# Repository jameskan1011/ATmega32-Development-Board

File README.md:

# ATmega32-Development-Board
ATmega32 Development Board with Latches and Buffers to minimize GPIO used.

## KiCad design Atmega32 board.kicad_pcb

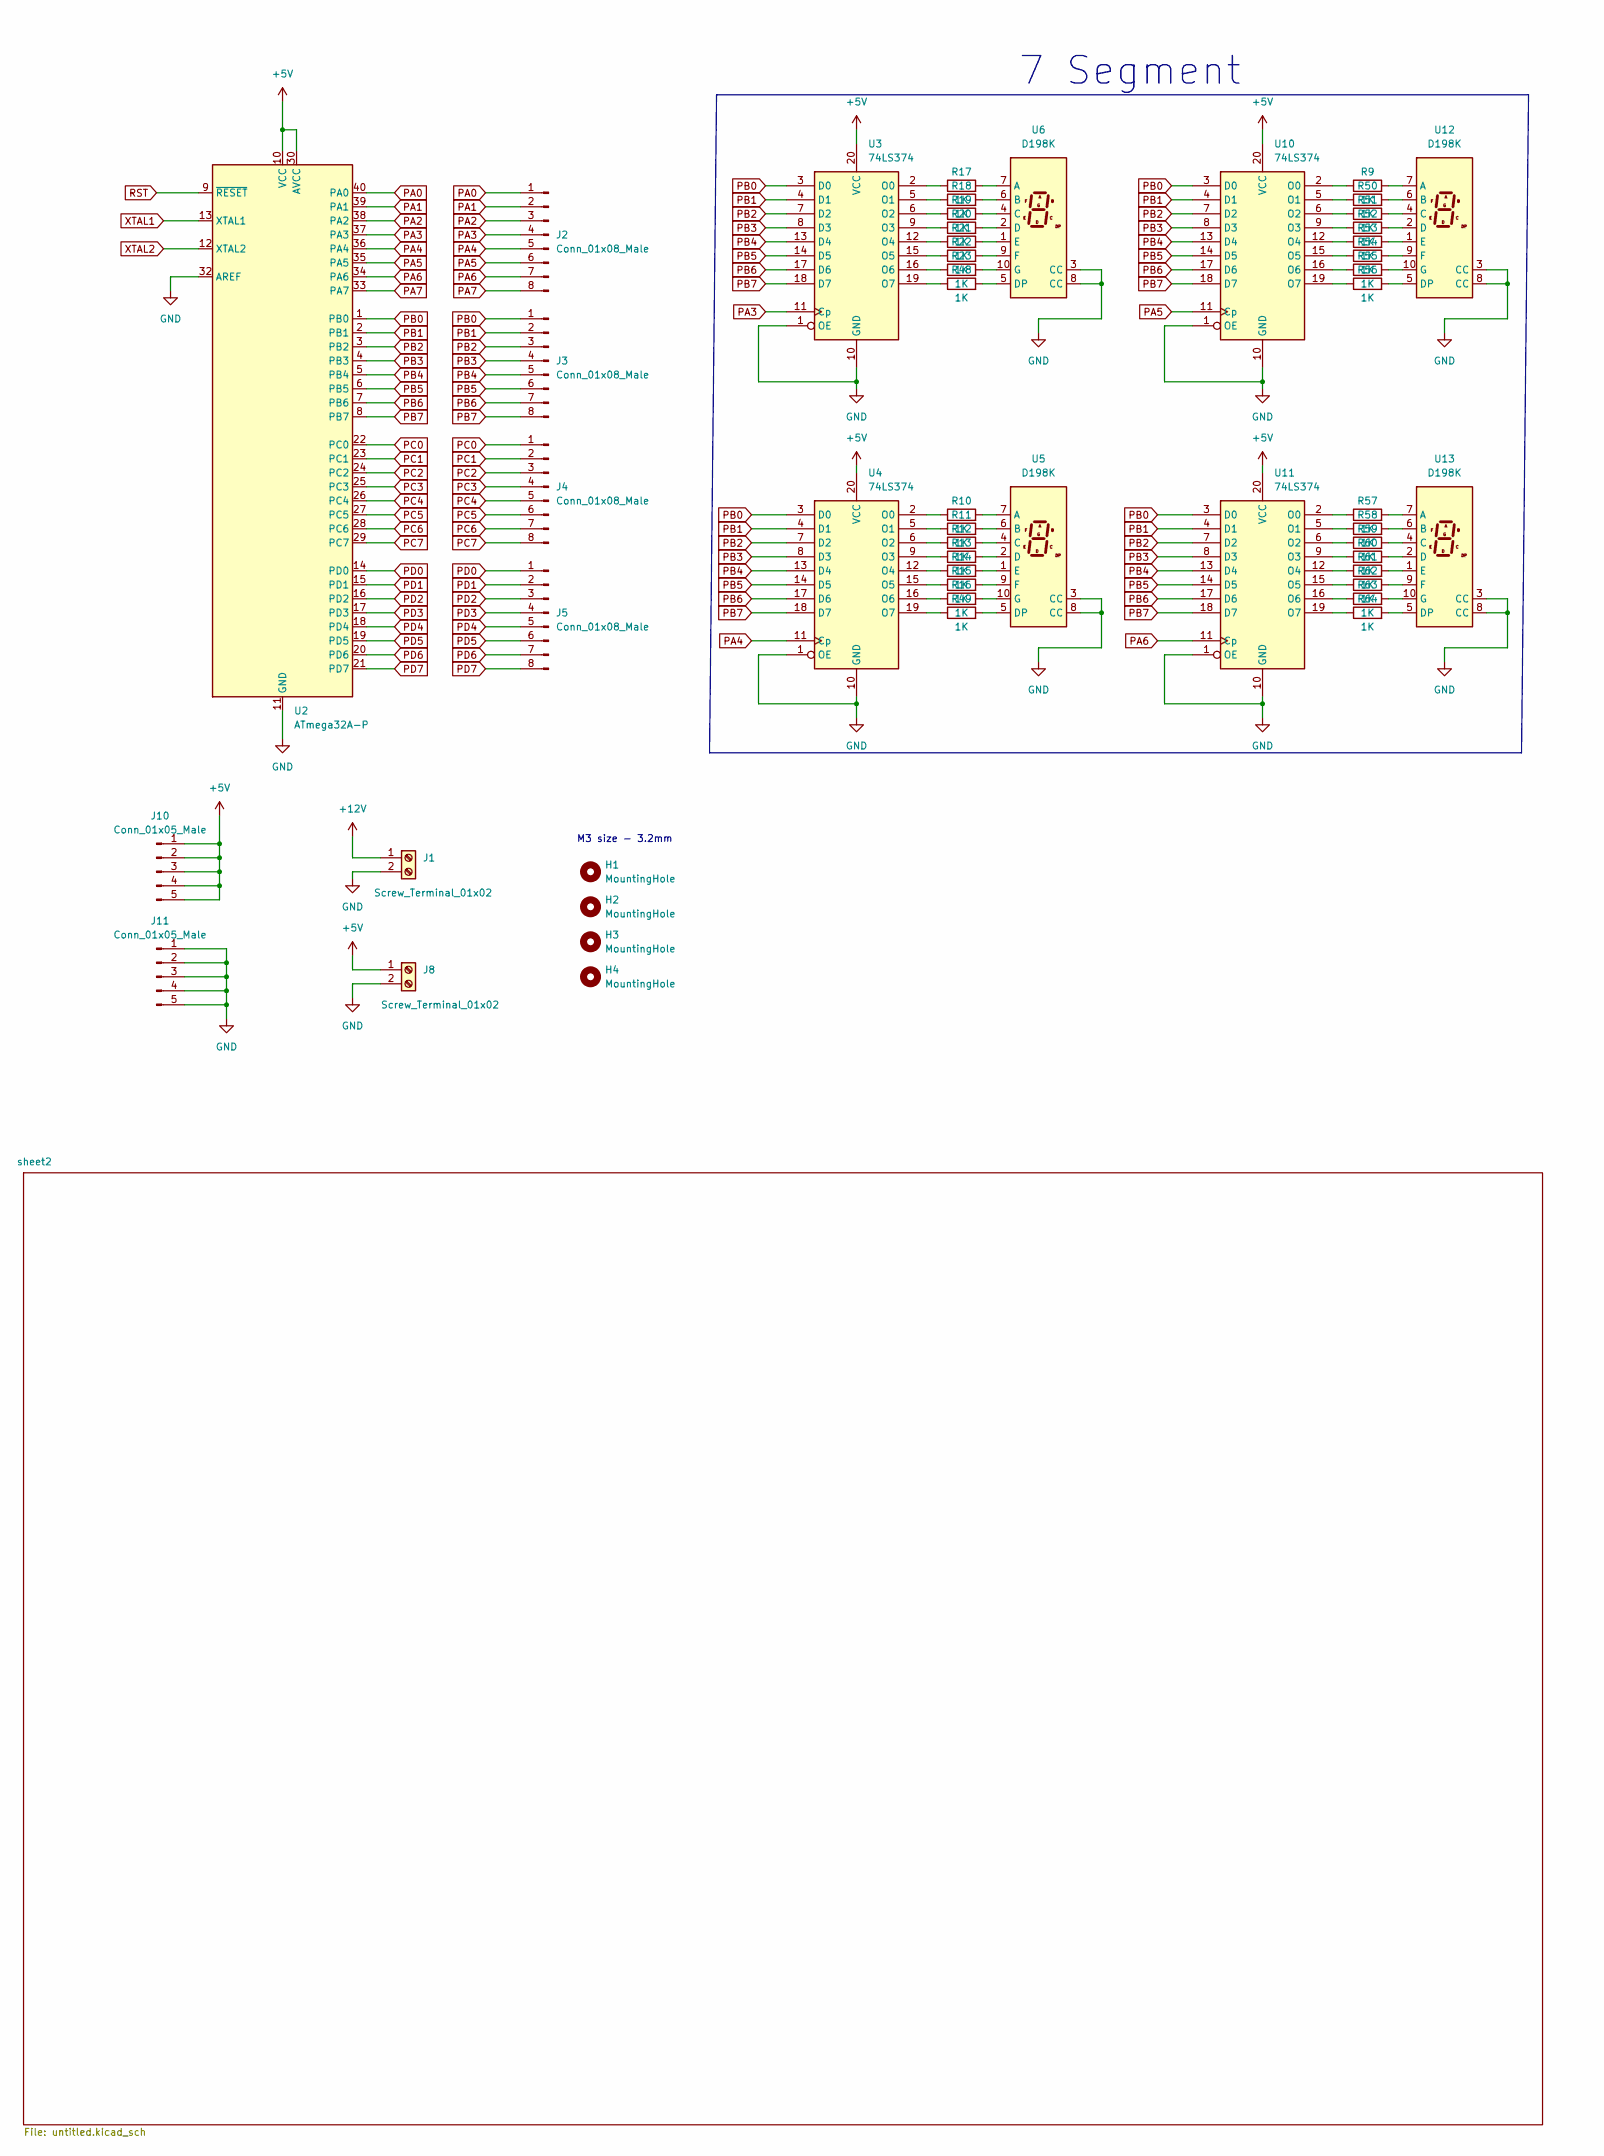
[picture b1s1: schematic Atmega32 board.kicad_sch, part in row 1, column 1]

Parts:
H1, H2, H3, H4: MountingHole; MountingHole_3.2mm_M3
J1, J8: Screw_Terminal_01x02; TerminalBlock_RND_205-00045_1x02_P5.00mm_Horizontal
J2, J3, J4, J5: Conn_01x08_Male; PinHeader_1x08_P2.54mm_Vertical
J10, J11: Conn_01x05_Male; PinHeader_1x05_P2.54mm_Vertical
R9, R10, R11, R12, R13, R14, R15, R16, R17, R18, R19, R20, R21, R22, R23, R48, R49, R50, R51, R52, R53, R54, R55, R56, R57, R58, R59, R60, R61, R62, R63, R64: 1K; R_0805_2012Metric_Pad1.20x1.40mm_HandSolder
U2: ATmega32A-P; DIP-40_W15.24mm
U3, U4, U10, U11: 74LS374; SOIC-20W_7.5x12.8mm_P1.27mm
U5, U6, U12, U13: D198K; 7SegmentLED_LTS6760_LTS6780

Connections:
+5V: J8.1, J10.1, J10.2, J10.3, J10.4, J10.5, U2.10 (VCC), U2.30 (AVCC), U3.20 (VCC), U4.20 (VCC), U10.20 (VCC), U11.20 (VCC); also elsewhere on the board
+12V: J1.1; also elsewhere on the board
GND: J1.2, J8.2, J11.1, J11.2, J11.3, J11.4, J11.5, U2.11 (GND), U2.31 (GND), U2.32 (AREF), U3.1 (OE), U3.10 (GND), U4.1 (OE), U4.10 (GND), U5.3 (CC), U5.8 (CC), U6.3 (CC), U6.8 (CC), U10.1 (OE), U10.10 (GND), U11.1 (OE), U11.10 (GND), U12.3 (CC), U12.8 (CC), U13.3 (CC), U13.8 (CC); also elsewhere on the board
unnamed: R17.1, U3.2 (O0)
unnamed: R18.1, U3.5 (O1)
unnamed: R19.1, U3.6 (O2)
unnamed: R20.1, U3.9 (O3)
unnamed: R21.1, U3.12 (O4)
unnamed: R22.1, U3.15 (O5)
unnamed: R23.1, U3.16 (O6)
unnamed: R48.1, U3.19 (O7)
unnamed: R10.1, U4.2 (O0)
unnamed: R11.1, U4.5 (O1)
unnamed: R12.1, U4.6 (O2)
unnamed: R13.1, U4.9 (O3)
unnamed: R14.1, U4.12 (O4)
unnamed: R15.1, U4.15 (O5)
unnamed: R16.1, U4.16 (O6)
unnamed: R49.1, U4.19 (O7)
unnamed: R10.2, U5.7 (A)
unnamed: R11.2, U5.6 (B)
unnamed: R12.2, U5.4 (C)
unnamed: R13.2, U5.2 (D)
unnamed: R49.2, U5.5 (DP)
unnamed: R14.2, U5.1 (E)
unnamed: R15.2, U5.9 (F)
unnamed: R16.2, U5.10 (G)
unnamed: R17.2, U6.7 (A)
unnamed: R18.2, U6.6 (B)
unnamed: R19.2, U6.4 (C)
unnamed: R20.2, U6.2 (D)
unnamed: R48.2, U6.5 (DP)
unnamed: R21.2, U6.1 (E)
unnamed: R22.2, U6.9 (F)
unnamed: R23.2, U6.10 (G)
unnamed: R9.1, U10.2 (O0)
unnamed: R50.1, U10.5 (O1)
unnamed: R51.1, U10.6 (O2)
unnamed: R52.1, U10.9 (O3)
unnamed: R53.1, U10.12 (O4)
unnamed: R54.1, U10.15 (O5)
unnamed: R55.1, U10.16 (O6)
unnamed: R56.1, U10.19 (O7)
unnamed: R57.1, U11.2 (O0)
unnamed: R58.1, U11.5 (O1)
unnamed: R59.1, U11.6 (O2)
unnamed: R60.1, U11.9 (O3)
unnamed: R61.1, U11.12 (O4)
unnamed: R62.1, U11.15 (O5)
unnamed: R63.1, U11.16 (O6)
unnamed: R64.1, U11.19 (O7)
unnamed: R9.2, U12.7 (A)
unnamed: R50.2, U12.6 (B)
unnamed: R51.2, U12.4 (C)
unnamed: R52.2, U12.2 (D)
unnamed: R56.2, U12.5 (DP)
unnamed: R53.2, U12.1 (E)
unnamed: R54.2, U12.9 (F)
unnamed: R55.2, U12.10 (G)
unnamed: R57.2, U13.7 (A)
unnamed: R58.2, U13.6 (B)
unnamed: R59.2, U13.4 (C)
unnamed: R60.2, U13.2 (D)
unnamed: R64.2, U13.5 (DP)
unnamed: R61.2, U13.1 (E)
unnamed: R62.2, U13.9 (F)
unnamed: R63.2, U13.10 (G)
PA0: J2.1, U2.40 (PA0); also elsewhere on the board
PA1: J2.2, U2.39 (PA1)
PA2: J2.3, U2.38 (PA2)
PA3: J2.4, U2.37 (PA3), U3.11 (Cp)
PA4: J2.5, U2.36 (PA4), U4.11 (Cp)
PA5: J2.6, U2.35 (PA5), U10.11 (Cp)
PA6: J2.7, U2.34 (PA6), U11.11 (Cp)
PA7: J2.8, U2.33 (PA7); also elsewhere on the board
PB0: J3.1, U2.1 (PB0), U3.3 (D0), U4.3 (D0), U10.3 (D0), U11.3 (D0); also elsewhere on the board
PB1: J3.2, U2.2 (PB1), U3.4 (D1), U4.4 (D1), U10.4 (D1), U11.4 (D1); also elsewhere on the board
PB2: J3.3, U2.3 (PB2), U3.7 (D2), U4.7 (D2), U10.7 (D2), U11.7 (D2); also elsewhere on the board
PB3: J3.4, U2.4 (PB3), U3.8 (D3), U4.8 (D3), U10.8 (D3), U11.8 (D3); also elsewhere on the board
PB4: J3.5, U2.5 (PB4), U3.13 (D4), U4.13 (D4), U10.13 (D4), U11.13 (D4); also elsewhere on the board
PB5: J3.6, U2.6 (PB5), U3.14 (D5), U4.14 (D5), U10.14 (D5), U11.14 (D5); also elsewhere on the board
PB6: J3.7, U2.7 (PB6), U3.17 (D6), U4.17 (D6), U10.17 (D6), U11.17 (D6); also elsewhere on the board
PB7: J3.8, U2.8 (PB7), U3.18 (D7), U4.18 (D7), U10.18 (D7), U11.18 (D7); also elsewhere on the board
PC0: J4.1, U2.22 (PC0)
PC1: J4.2, U2.23 (PC1)
PC2: J4.3, U2.24 (PC2)
PC3: J4.4, U2.25 (PC3)
PC4: J4.5, U2.26 (PC4)
PC5: J4.6, U2.27 (PC5)
PC6: J4.7, U2.28 (PC6)
PC7: J4.8, U2.29 (PC7)
PD0: J5.1, U2.14 (PD0); also elsewhere on the board
PD1: J5.2, U2.15 (PD1); also elsewhere on the board
PD2: J5.3, U2.16 (PD2); also elsewhere on the board
PD3: J5.4, U2.17 (PD3); also elsewhere on the board
PD4: J5.5, U2.18 (PD4)
PD5: J5.6, U2.19 (PD5)
PD6: J5.7, U2.20 (PD6)
PD7: J5.8, U2.21 (PD7)
RST: U2.9 (~RESET); also elsewhere on the board
XTAL1: U2.13 (XTAL1); also elsewhere on the board
XTAL2: U2.12 (XTAL2); also elsewhere on the board

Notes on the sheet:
M3 size - 3.2mm
7 Segment

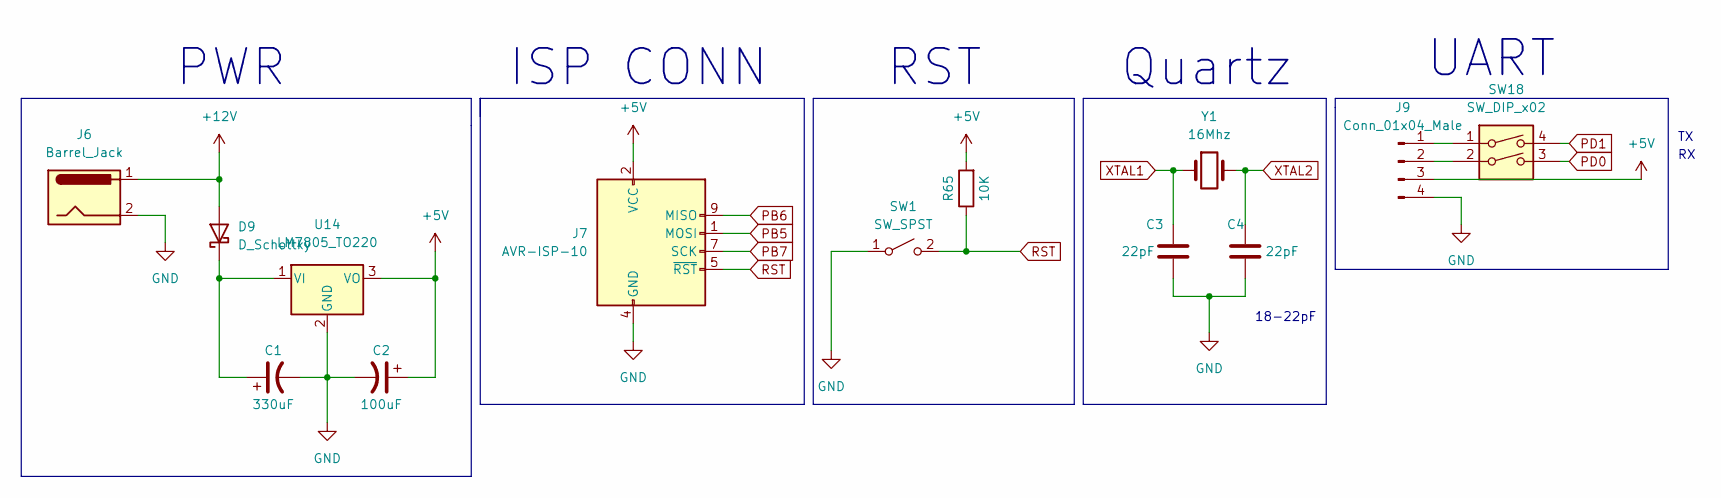
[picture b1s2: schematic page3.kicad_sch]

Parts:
C1: 330uF; CP_Radial_D7.5mm_P2.50mm
C2: 100uF; CP_Radial_D7.5mm_P2.50mm
C3, C4: 22pF; C_0805_2012Metric
D9: D_Schottky; D_SMA
J6: Barrel_Jack; BarrelJack_Wuerth_6941xx301002
J7: AVR-ISP-10; IDC-Header_2x05_P2.54mm_Vertical
J9: Conn_01x04_Male; PinHeader_1x04_P2.54mm_Vertical
R65: 10K; R_0805_2012Metric_Pad1.20x1.40mm_HandSolder
SW1: SW_SPST; SW_PUSH_6mm
SW18: SW_DIP_x02; SW_DIP_SPSTx02_Slide_9.78x7.26mm_W7.62mm_P2.54mm
U14: LM7805_TO220; TO-220-3_Vertical
Y1: 16Mhz; Crystal_HC49-U_Vertical

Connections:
+5V: C2.1, J7.2 (VCC), J9.3, R65.2, U14.3 (VO); also elsewhere on the board
+12V: D9.2 (A), J6.1; also elsewhere on the board
GND: C1.2, C2.2, C3.1, C4.1, J6.2, J7.4 (GND), J7.6 (GND), J7.8 (GND), J7.10 (GND), J9.4, SW1.1 (A), U14.2 (GND); also elsewhere on the board
unnamed: C1.1, D9.1 (K), U14.1 (VI)
unnamed: J9.1, SW18.1
unnamed: J9.2, SW18.2
PB5: J7.1 (MOSI); also elsewhere on the board
PB6: J7.9 (MISO); also elsewhere on the board
PB7: J7.7 (SCK); also elsewhere on the board
PD0: SW18.3; also elsewhere on the board
PD1: SW18.4; also elsewhere on the board
RST: J7.5 (~RST), R65.1, SW1.2 (B); also elsewhere on the board
XTAL1: C3.2, Y1.1; also elsewhere on the board
XTAL2: C4.2, Y1.2; also elsewhere on the board

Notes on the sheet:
Quartz
PWR
18-22pF
UART
ISP CONN
RST

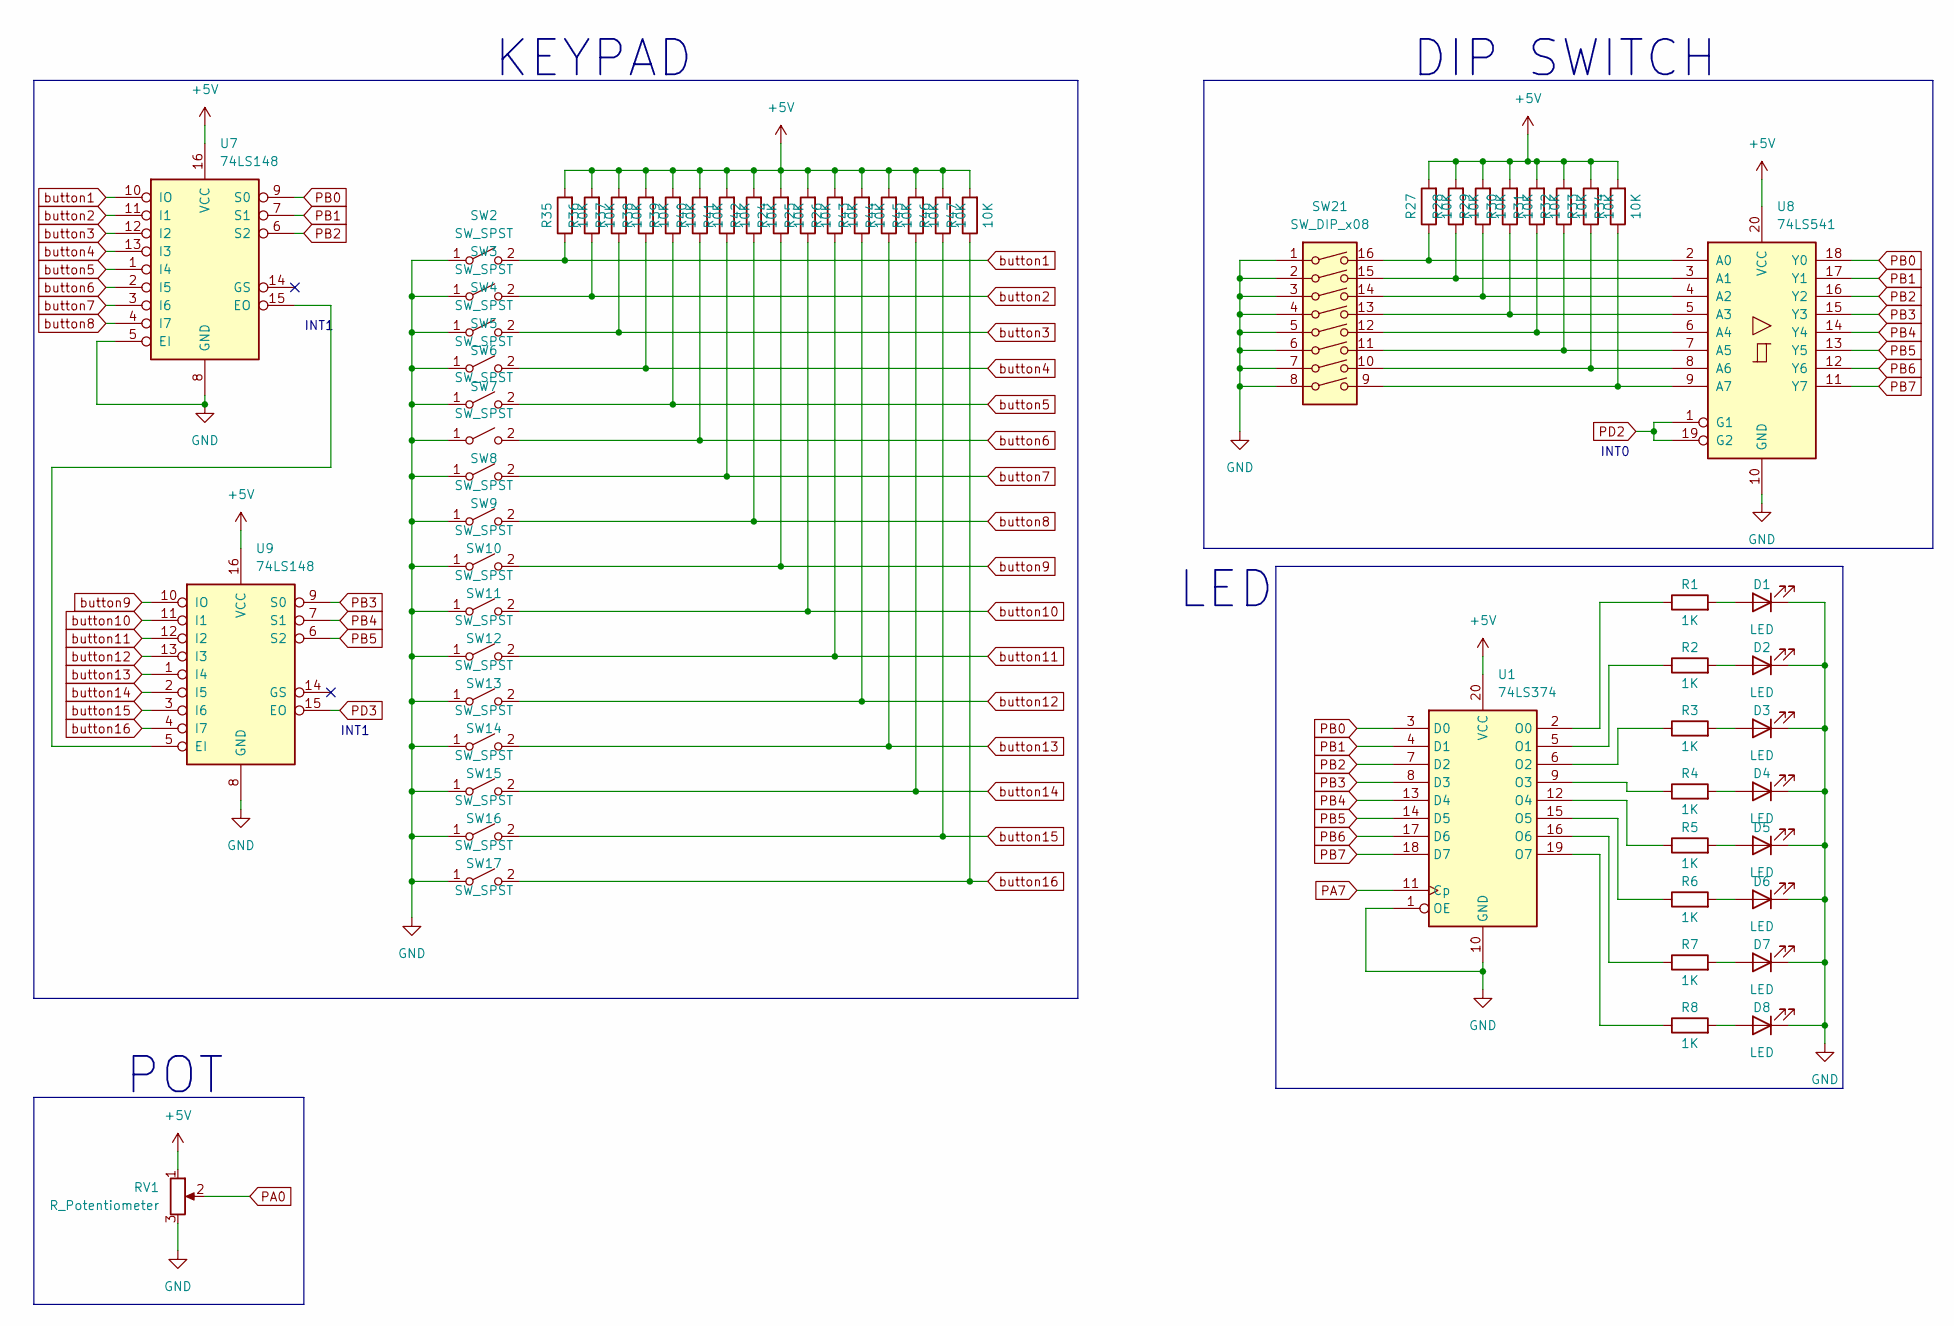
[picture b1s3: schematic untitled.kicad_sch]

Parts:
D1, D2, D3, D4, D5, D6, D7, D8: LED; LED_0805_2012Metric
R1, R2, R3, R4, R5, R6, R7, R8: 1K; R_0805_2012Metric_Pad1.20x1.40mm_HandSolder
R24, R25, R26, R27, R28, R29, R30, R31, R32, R33, R34, R35, R36, R37, R38, R39, R40, R41, R42, R43, R44, R45, R46, R47: 10K; R_0805_2012Metric_Pad1.20x1.40mm_HandSolder
RV1: R_Potentiometer; Potentiometer_Runtron_RM-065_Vertical
SW2, SW3, SW4, SW5, SW6, SW7, SW8, SW9, SW10, SW11, SW12, SW13, SW14, SW15, SW16, SW17: SW_SPST; SW_PUSH_6mm
SW21: SW_DIP_x08; SW_DIP_SPSTx08_Slide_9.78x22.5mm_W7.62mm_P2.54mm
U1: 74LS374; SOIC-20W_7.5x12.8mm_P1.27mm
U7, U9: 74LS148; SOIC-16W_5.3x10.2mm_P1.27mm
U8: 74LS541; SOIC-20W_7.5x12.8mm_P1.27mm

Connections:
+5V: R24.2, R25.2, R26.2, R27.2, R28.2, R29.2, R30.2, R31.2, R32.2, R33.2, R34.2, R35.2, R36.2, R37.2, R38.2, R39.2, R40.2, R41.2, R42.2, R43.2, R44.2, R45.2, R46.2, R47.2, RV1.1, U1.20 (VCC), U7.16 (VCC), U8.20 (VCC), U9.16 (VCC); also elsewhere on the board
GND: D1.1 (K), D2.1 (K), D3.1 (K), D4.1 (K), D5.1 (K), D6.1 (K), D7.1 (K), D8.1 (K), RV1.3, SW2.1 (A), SW3.1 (A), SW4.1 (A), SW5.1 (A), SW6.1 (A), SW7.1 (A), SW8.1 (A), SW9.1 (A), SW10.1 (A), SW11.1 (A), SW12.1 (A), SW13.1 (A), SW14.1 (A), SW15.1 (A), SW16.1 (A), SW17.1 (A), SW21.1, SW21.2, SW21.3, SW21.4, SW21.5, SW21.6, SW21.7, SW21.8, U1.1 (OE), U1.10 (GND), U7.5 (EI), U7.8 (GND), U8.10 (GND), U9.8 (GND); also elsewhere on the board
unnamed: D1.2 (A), R1.2
unnamed: D2.2 (A), R2.2
unnamed: D3.2 (A), R3.2
unnamed: D4.2 (A), R4.2
unnamed: D5.2 (A), R5.2
unnamed: D6.2 (A), R6.2
unnamed: D7.2 (A), R7.2
unnamed: D8.2 (A), R8.2
unnamed: R1.1, U1.2 (O0)
unnamed: R2.1, U1.5 (O1)
unnamed: R3.1, U1.6 (O2)
unnamed: R4.1, U1.9 (O3)
unnamed: R5.1, U1.12 (O4)
unnamed: R6.1, U1.15 (O5)
unnamed: R7.1, U1.16 (O6)
unnamed: R8.1, U1.19 (O7)
unnamed: U7.15 (EO), U9.5 (EI)
unnamed: R27.1, SW21.16, U8.2 (A0)
unnamed: R28.1, SW21.15, U8.3 (A1)
unnamed: R29.1, SW21.14, U8.4 (A2)
unnamed: R30.1, SW21.13, U8.5 (A3)
unnamed: R31.1, SW21.12, U8.6 (A4)
unnamed: R32.1, SW21.11, U8.7 (A5)
unnamed: R33.1, SW21.10, U8.8 (A6)
unnamed: R34.1, SW21.9, U8.9 (A7)
PA0: RV1.2; also elsewhere on the board
PA7: U1.11 (Cp); also elsewhere on the board
PB0: U1.3 (D0), U7.9 (S0), U8.18 (Y0); also elsewhere on the board
PB1: U1.4 (D1), U7.7 (S1), U8.17 (Y1); also elsewhere on the board
PB2: U1.7 (D2), U7.6 (S2), U8.16 (Y2); also elsewhere on the board
PB3: U1.8 (D3), U8.15 (Y3), U9.9 (S0); also elsewhere on the board
PB4: U1.13 (D4), U8.14 (Y4), U9.7 (S1); also elsewhere on the board
PB5: U1.14 (D5), U8.13 (Y5), U9.6 (S2); also elsewhere on the board
PB6: U1.17 (D6), U8.12 (Y6); also elsewhere on the board
PB7: U1.18 (D7), U8.11 (Y7); also elsewhere on the board
PD2: U8.1 (G1), U8.19 (G2); also elsewhere on the board
PD3: U9.15 (EO); also elsewhere on the board
button1: R35.1, SW2.2 (B), U7.10 (IO)
button2: R36.1, SW3.2 (B), U7.11 (I1)
button3: R37.1, SW4.2 (B), U7.12 (I2)
button4: R38.1, SW5.2 (B), U7.13 (I3)
button5: R39.1, SW6.2 (B), U7.1 (I4)
button6: R40.1, SW7.2 (B), U7.2 (I5)
button7: R41.1, SW8.2 (B), U7.3 (I6)
button8: R42.1, SW9.2 (B), U7.4 (I7)
button9: R24.1, SW10.2 (B), U9.10 (IO)
button10: R25.1, SW11.2 (B), U9.11 (I1)
button11: R26.1, SW12.2 (B), U9.12 (I2)
button12: R43.1, SW13.2 (B), U9.13 (I3)
button13: R44.1, SW14.2 (B), U9.1 (I4)
button14: R45.1, SW15.2 (B), U9.2 (I5)
button15: R46.1, SW16.2 (B), U9.3 (I6)
button16: R47.1, SW17.2 (B), U9.4 (I7)

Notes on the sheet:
KEYPAD
INT0
INT1
LED
POT
DIP SWITCH

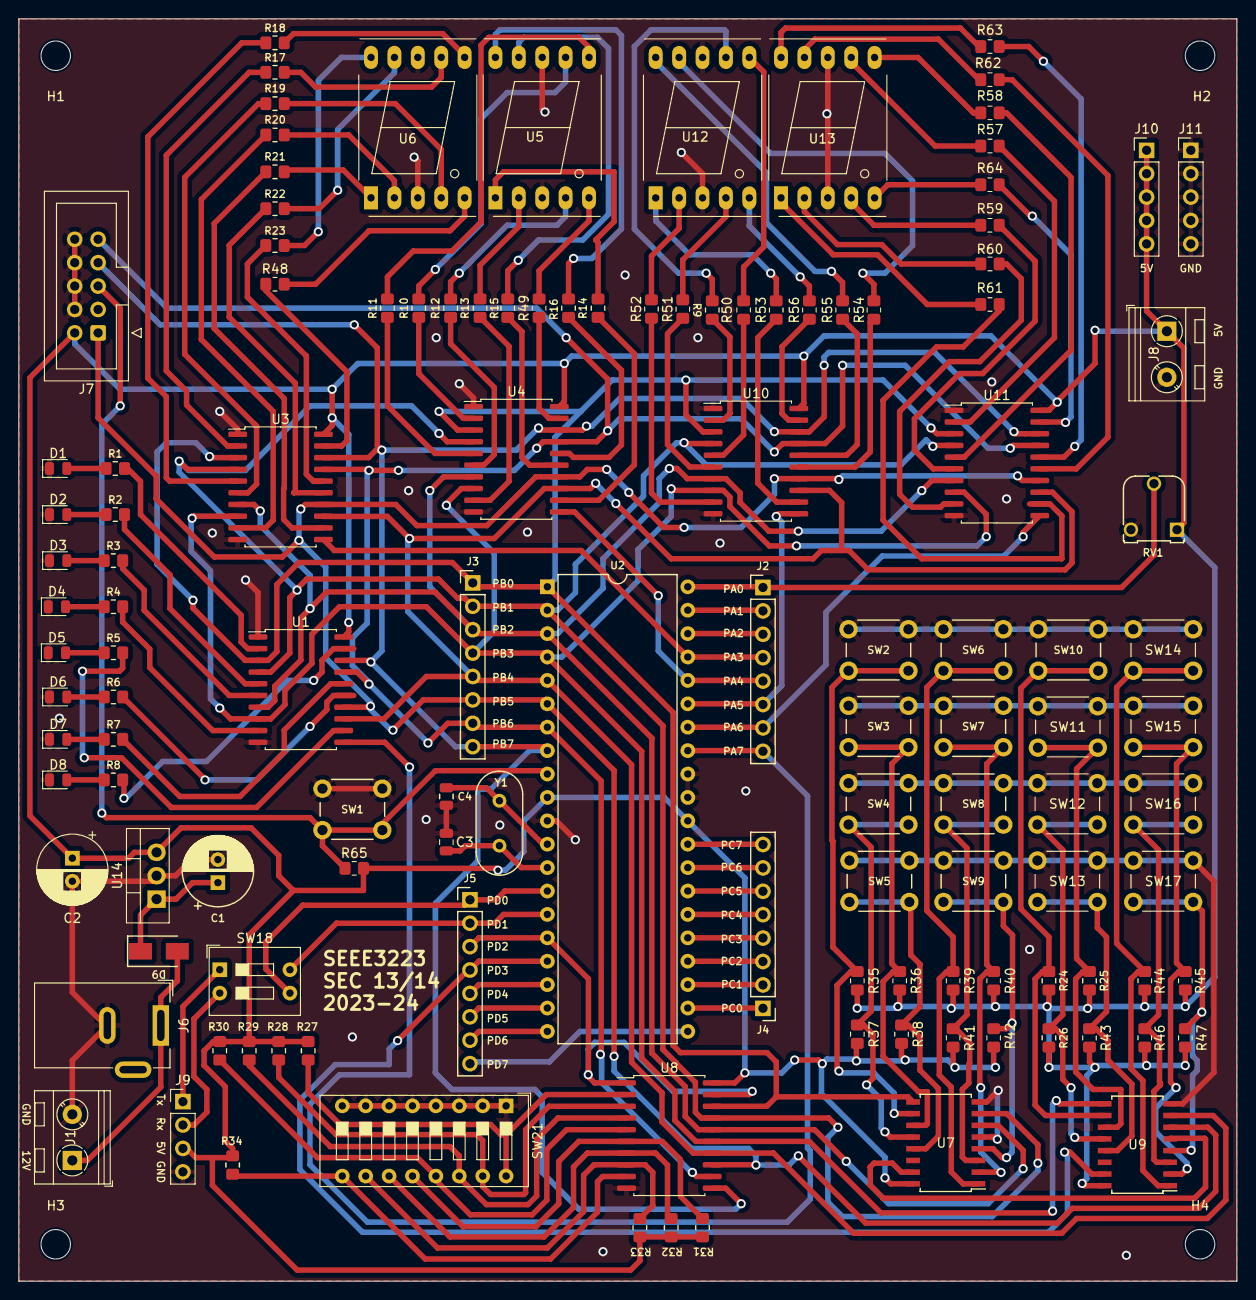
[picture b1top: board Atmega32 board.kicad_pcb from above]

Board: 2 copper layers, 132.2 x 137.0 mm, 128 parts (0 on the bottom side), 146 nets.

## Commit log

2024-02-25 latest
2024-02-25 init commit
